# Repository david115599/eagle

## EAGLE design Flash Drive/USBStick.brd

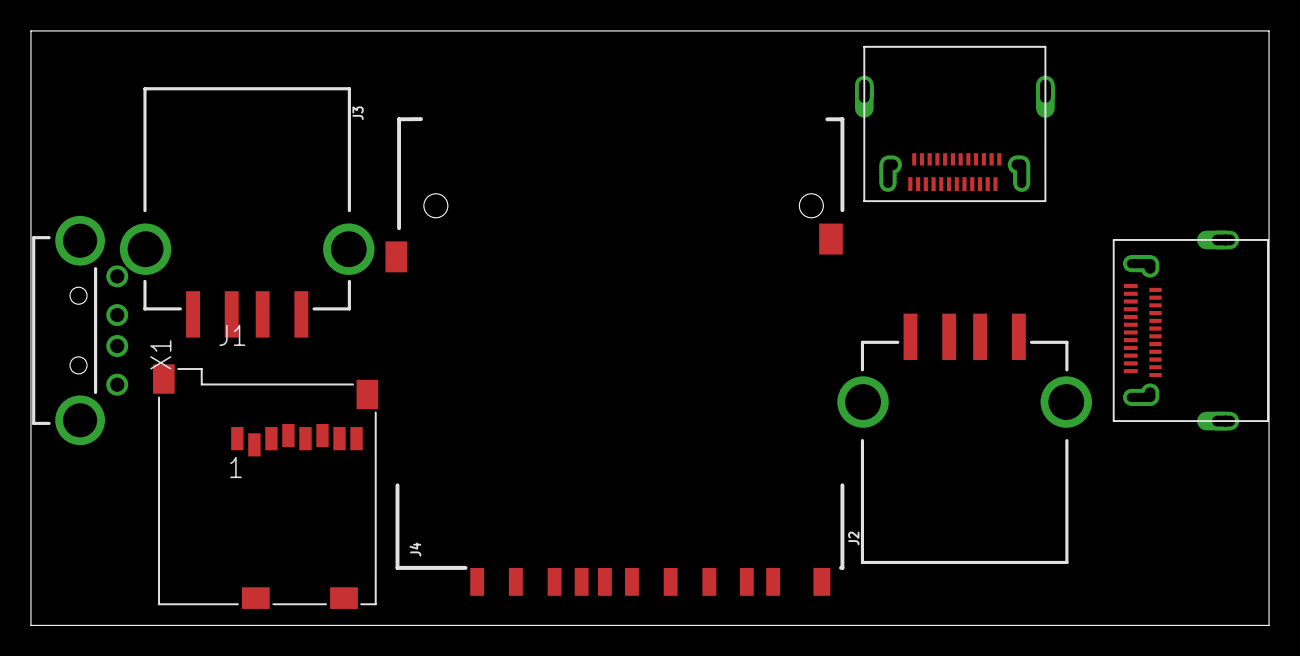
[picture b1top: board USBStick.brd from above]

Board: 2 copper layers, 80.0 x 38.4 mm, 7 parts (0 on the bottom side), 2 nets, no tracks yet.

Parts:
J1: 693071010811
J2, J3: USB_A_SMT_FEMALE; USB-A-S-SILK-FEMALE
J4: SD_CARD_SOCKET; SD
U$1, U$2: USB-TYPE-C; USB-TYPE-C-SMT
X1: USB-A-H

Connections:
GND: J2.GND, J3.GND, U$1.1, U$1.12, U$1.B1, U$1.B12, U$2.1, U$2.12, U$2.B1, U$2.B12
VBUS: J2.VBUS, J3.VBUS

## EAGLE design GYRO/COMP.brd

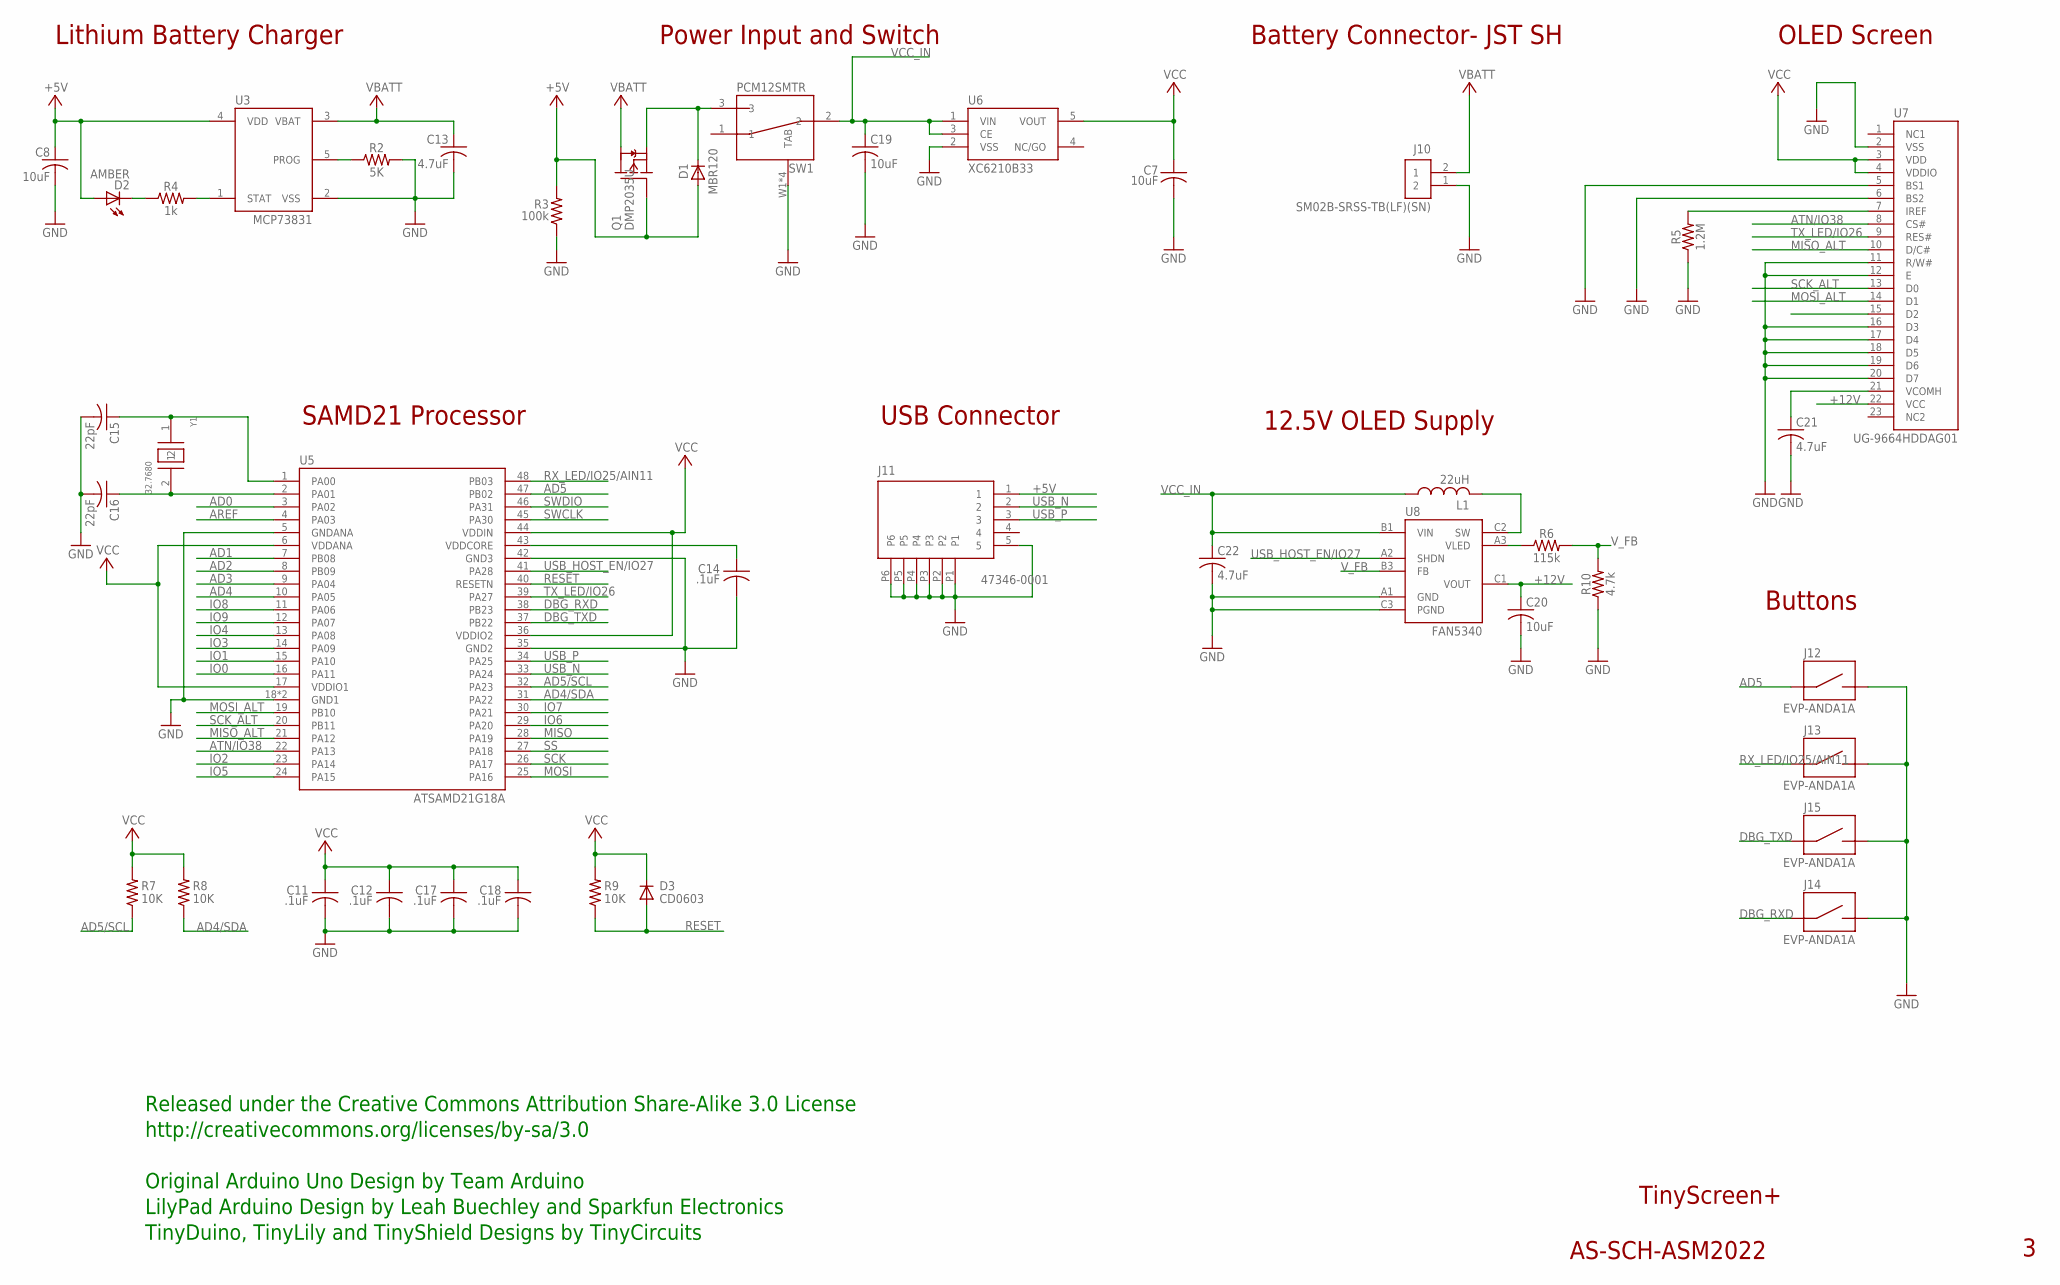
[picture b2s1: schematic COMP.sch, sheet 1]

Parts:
C7, C8: 10uF; C0603; MPN C0603X5R1A104K030BC
C11, C12, C14, C17, C18: .1uF; C0402; MPN GRM155R61C104KA88D
C13: 4.7uF; C0603; MPN C0603X5R0J474K030BC
C15, C16: 22pF; C0402; MPN C0402C220C5GACTU
C19, C20: 10uF; C0805; MPN LMK212BJ106KG-T
C21: 4.7uF; 1206_CAP_TANT; MPN TAJA475K020RNJ
C22: 4.7uF; C0402; MPN C0402C475M9PACTU
D1: MBR120; SOD-123FL; MPN MBR120LSFT1G
D2: AMBER; LNJ_LED; MPN LNJ426W83RA1
D3: CD0603; 0603; MPN CD0603-S01575
J10: SM02B-SRSS-TB(LF)(SN); JST_SH_2X1; MPN SM02B-SRSS-TB (LF)(SN)
J11: 47346-0001; MICRO_USB; MPN 47346-0001
J12, J13, J14, J15: EVP-ANDA1A; PTS840GKP; MPN EVP-ANDA1A
L1: 22uH; R0805; PARTNO AS-ITM-00281
Q1: DMP2035U; SOT23; MPN DMP2035U
R2: 5K; 0402
R3: 100k; 0402; MPN CRG0402J100K/10
R4: 1k; 0402; MPN CRCW04021K00FKTD
R5: 1.2M; 0402; PARTNO AS-ITM-00280
R6: 115k; 0402; MPN CPF0402B115KE1
R7, R8, R9: 10K; 0402; MPN TNPW040210K0BEED
R10: 4.7k; 0402; MPN 373-4.7K
SW1: PCM12SMTR
U3: MCP73831; SOT-23
U5: ATSAMD21G18A; QFN48; PARTNO AS-ITM-00273
U6: XC6210B33; SOT-25
U7: UG-9664HDDAG01; OLED_DISPLAY
U8: FAN5340; WLCSP8_1_57X1_57
Y1: 32.7680; ABS06; PARTNO AS-ITM-00279

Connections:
+5V: C8.1, D1.A, D2.A, J11.1, Q1.B (G), R3.2, U3.4 (VDD)
+12V: C20.1, U7.22 (VCC), U8.C1 (VOUT)
AD0: U5.3 (PA02)
AD1: U5.7 (PB08)
AD2: U5.8 (PB09)
AD3: U5.9 (PA04)
AD4: U5.10 (PA05)
AD4/SDA: R8.1, U5.31 (PA22); also elsewhere on the board
AD5: J12.1, J12.2 (1), U5.47 (PB02)
AD5/SCL: R7.1, U5.32 (PA23); also elsewhere on the board
AREF: U5.4 (PA03)
ATN/IO38: U5.22 (PA13), U7.8 (CS#)
DBG_RXD: J14.1, J14.2 (1), U5.38 (PB23)
DBG_TXD: J15.1, J15.2 (1), U5.37 (PB22)
GND: C7.2, C8.2, C11.2, C12.2, C13.2, C14.2, C15.2, C16.2, C17.2, C18.2, C19.2, C20.2, C21.2, C22.2, J10.1 (2), J11.5, J11.P1, J11.P2, J11.P3, J11.P4, J11.P5, J11.P6, J12.3 (2), J12.4 (2), J13.3 (2), J13.4 (2), J14.3 (2), J14.4 (2), J15.3 (2), J15.4 (2), R2.2, R3.1, R5.1, R10.1, SW1.W1 (TAB), SW1.W2 (TAB), SW1.W3 (TAB), SW1.W4 (TAB), U3.2 (VSS), U5.5 (GNDANA), U5.18 (GND1), U5.35 (GND2), U5.42 (GND3), U5.EXP (GND1), U6.2 (VSS), U7.2 (VSS), U7.5 (BS1), U7.6 (BS2), U7.11 (R/W#), U7.12 (E), U7.16 (D3), U7.17 (D4), U7.18 (D5), U7.19 (D6), U7.20 (D7), U8.A1 (GND), U8.C3 (PGND); also elsewhere on the board
IO0: U5.16 (PA11)
IO1: U5.15 (PA10)
IO2: U5.23 (PA14)
IO3: U5.14 (PA09)
IO4: U5.13 (PA08)
IO5: U5.24 (PA15)
IO6: U5.29 (PA20)
IO7: U5.30 (PA21)
IO8: U5.11 (PA06)
IO9: U5.12 (PA07)
MISO: U5.28 (PA19)
MISO_ALT: U5.21 (PA12), U7.10 (D/C#)
MOSI: U5.25 (PA16)
MOSI_ALT: U5.19 (PB10), U7.14 (D1)
unnamed: D1.C, Q1.E (S), SW1.3
unnamed: C15.1, U5.1 (PA00), Y1.1
unnamed: D2.C, R4.1
unnamed: R2.1, U3.5 (PROG)
unnamed: R4.2, U3.1 (STAT)
unnamed: C16.1, U5.2 (PA01), Y1.2
unnamed: C14.1, U5.43 (VDDCORE)
unnamed: L1.2, U8.C2 (SW)
unnamed: R5.2, U7.7 (IREF)
unnamed: C21.1, U7.21 (VCOMH)
unnamed: R6.1, U8.A3 (VLED)
RESET: D3.A, R9.1, U5.40 (RESETN)
RX_LED/IO25/AIN11: J13.1, J13.2 (1), U5.48 (PB03)
SCK: U5.26 (PA17)
SCK_ALT: U5.20 (PB11), U7.13 (D0)
SS: U5.27 (PA18)
SWCLK: U5.45 (PA30)
SWDIO: U5.46 (PA31)
TX_LED/IO26: U5.39 (PA27), U7.9 (RES#)
USB_HOST_EN/IO27: U5.41 (PA28), U8.A2 (SHDN)
USB_N: J11.2, U5.33 (PA24)
USB_P: J11.3, U5.34 (PA25)
VBATT: C13.1, J10.2 (1), Q1.C (D), U3.3 (VBAT)
VCC: C7.1, C11.1, C12.1, C17.1, C18.1, D3.C, R7.2, R8.2, R9.2, U5.6 (VDDANA), U5.17 (VDDIO1), U5.36 (VDDIO2), U5.44 (VDDIN), U6.5 (VOUT), U7.3 (VDD), U7.4 (VDDIO); also elsewhere on the board
VCC_IN: C19.1, C22.1, L1.1, SW1.2, U6.1 (VIN), U6.3 (CE), U8.B1 (VIN)
V_FB: R6.2, R10.2, U8.B3 (FB)

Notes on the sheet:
SAMD21 Processor
Power Input and Switch
TinyScreen+
AS-SCH-ASM2022
Released under the Creative Commons Attribution Share-Alike 3.0 License
http://creativecommons.org/licenses/by-sa/3.0
Original Arduino Uno Design by Team Arduino
TinyDuino, TinyLily and TinyShield Designs by TinyCircuits
LilyPad Arduino Design by Leah Buechley and Sparkfun Electronics
Lithium Battery Charger
Battery Connector- JST SH
OLED Screen
12.5V OLED Supply
Buttons
USB Connector

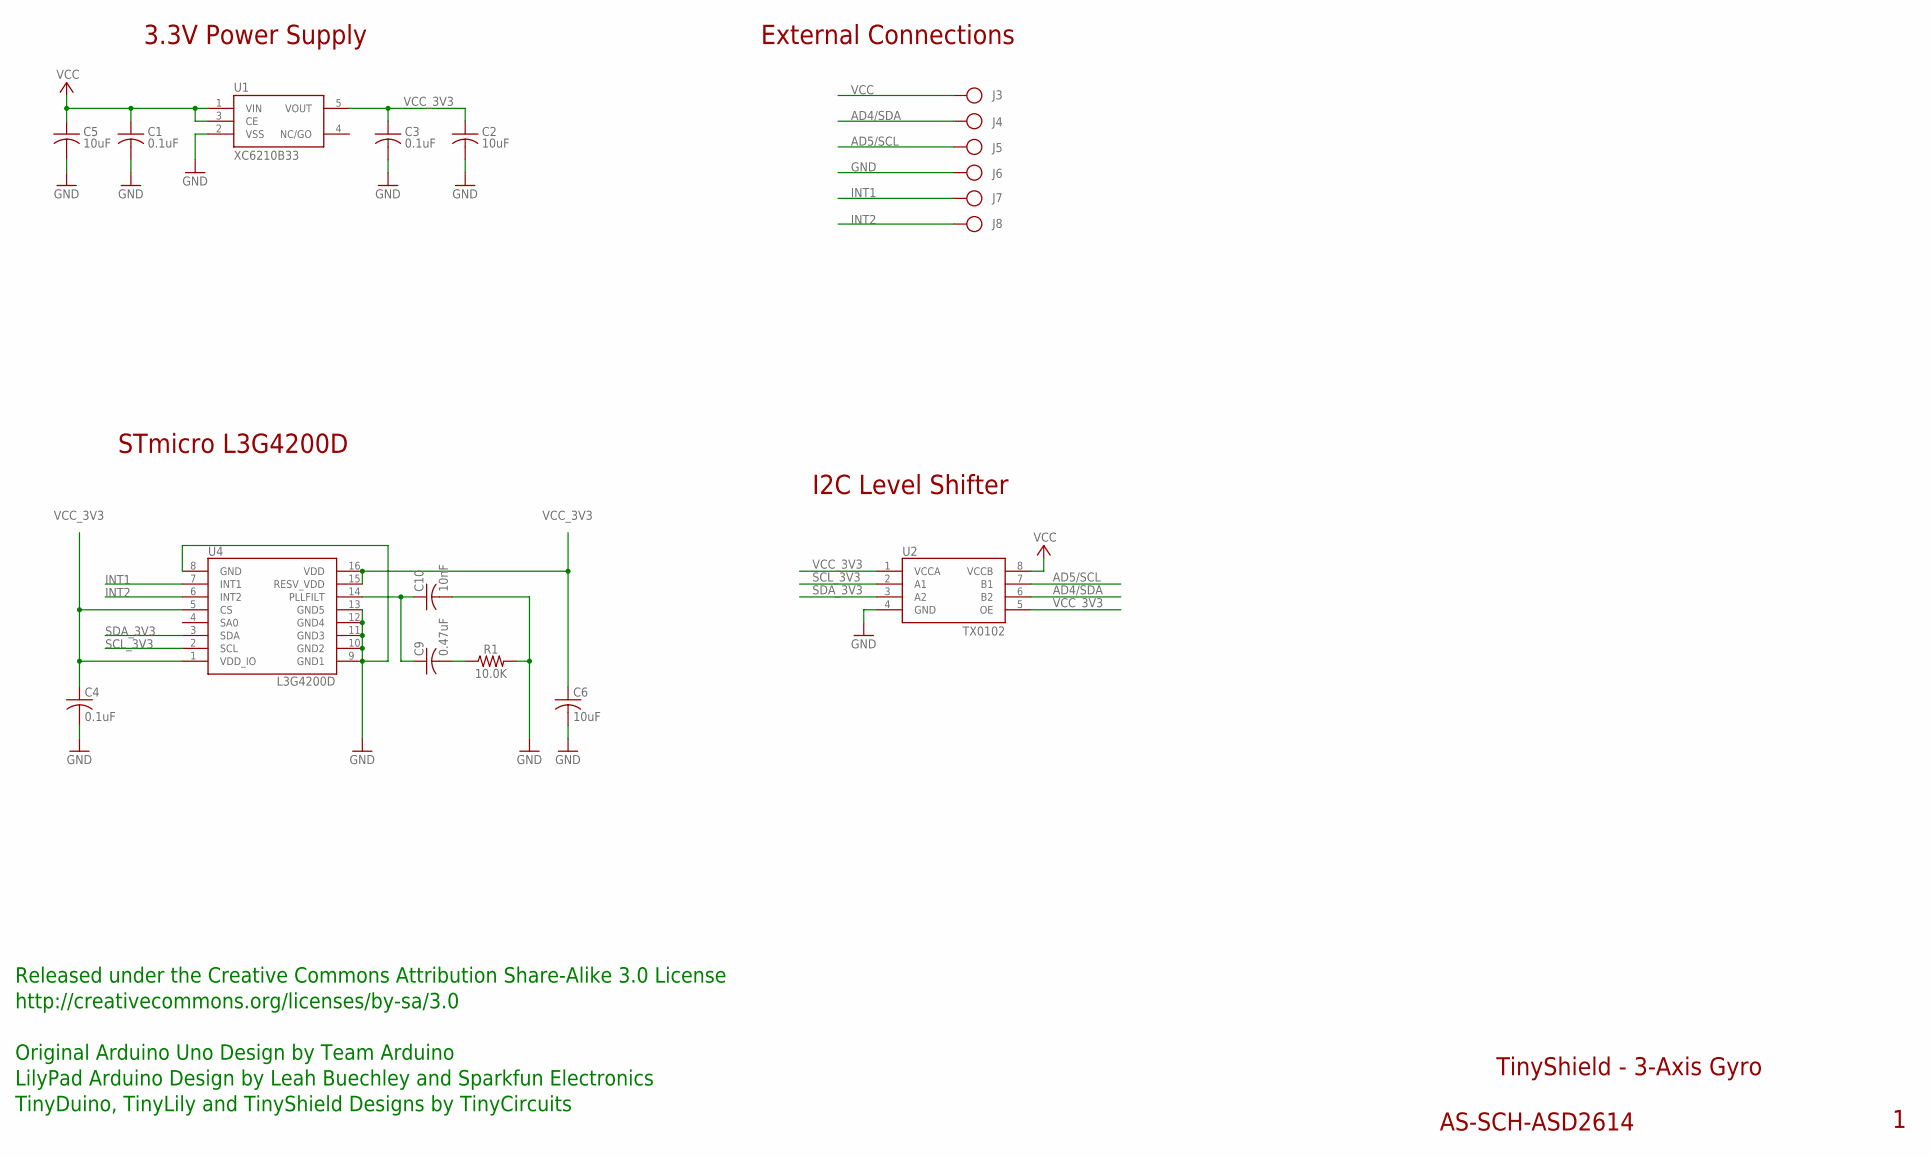
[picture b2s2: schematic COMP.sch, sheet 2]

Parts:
C1, C3, C4: 0.1uF; C0402; MPN GRM155R61A104JA01D
C2, C5: 10uF; C0805; MPN LMK212BJ106KG-T
C6: 10uF; C0603; MPN C0603X5R1A104K030BC
C9: 0.47uF; C0402@1; MPN GRM155R60J474KE19D
C10: 10nF; 0402@1; MPN VJ0402V103ZXACW1BC
J3, J4, J5, J6, J7, J8: PIN_1X.1"; 1X.1"
R1: 10.0K; 0402; MPN CRCW120610K0FKTA
U1: XC6210B33; SOT-25
U2: TX0102; DQE(R-PX2SON-N8)
U4: L3G4200D

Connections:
AD4/SDA: J4.1, U2.6 (B2); also elsewhere on the board
AD5/SCL: J5.1, U2.7 (B1); also elsewhere on the board
GND: C1.2, C2.2, C3.2, C4.2, C5.2, C6.2, C10.2, J6.1, R1.2, U1.2 (VSS), U2.4 (GND), U4.8 (GND), U4.9 (GND1), U4.10 (GND2), U4.11 (GND3), U4.12 (GND4), U4.13 (GND5); also elsewhere on the board
INT1: J7.1, U4.7 (INT1)
INT2: J8.1, U4.6 (INT2)
unnamed: C9.2, R1.1
unnamed: C9.1, C10.1, U4.14 (PLLFILT)
SCL_3V3: U2.2 (A1), U4.2 (SCL)
SDA_3V3: U2.3 (A2), U4.3 (SDA)
VCC: C1.1, C5.1, J3.1, U1.1 (VIN), U1.3 (CE), U2.8 (VCCB); also elsewhere on the board
VCC_3V3: C2.1, C3.1, C4.1, C6.1, U1.5 (VOUT), U2.1 (VCCA), U2.5 (OE), U4.1 (VDD_IO), U4.5 (CS), U4.15 (RESV_VDD), U4.16 (VDD)

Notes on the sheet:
TinyShield - 3-Axis Gyro
AS-SCH-ASD2614
Released under the Creative Commons Attribution Share-Alike 3.0 License
http://creativecommons.org/licenses/by-sa/3.0
LilyPad Arduino Design by Leah Buechley and Sparkfun Electronics
TinyDuino, TinyLily and TinyShield Designs by TinyCircuits
Original Arduino Uno Design by Team Arduino
External Connections
3.3V Power Supply
I2C Level Shifter
STmicro L3G4200D

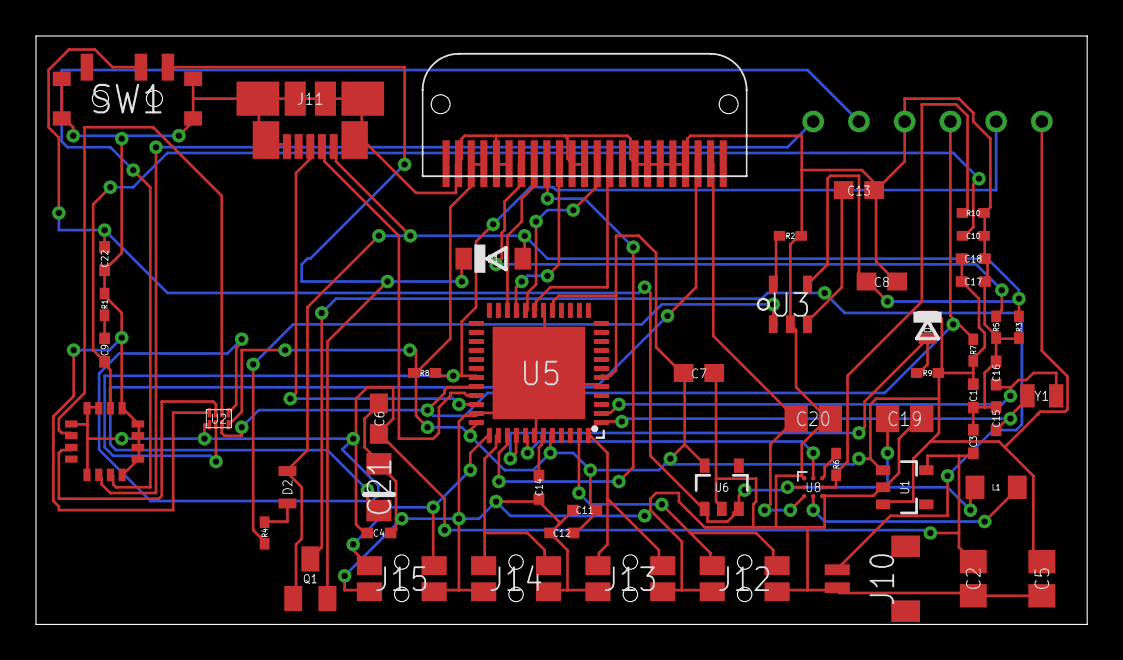
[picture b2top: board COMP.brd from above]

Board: 2 copper layers, 58.4 x 32.7 mm, 59 parts (0 on the bottom side), 40 nets.

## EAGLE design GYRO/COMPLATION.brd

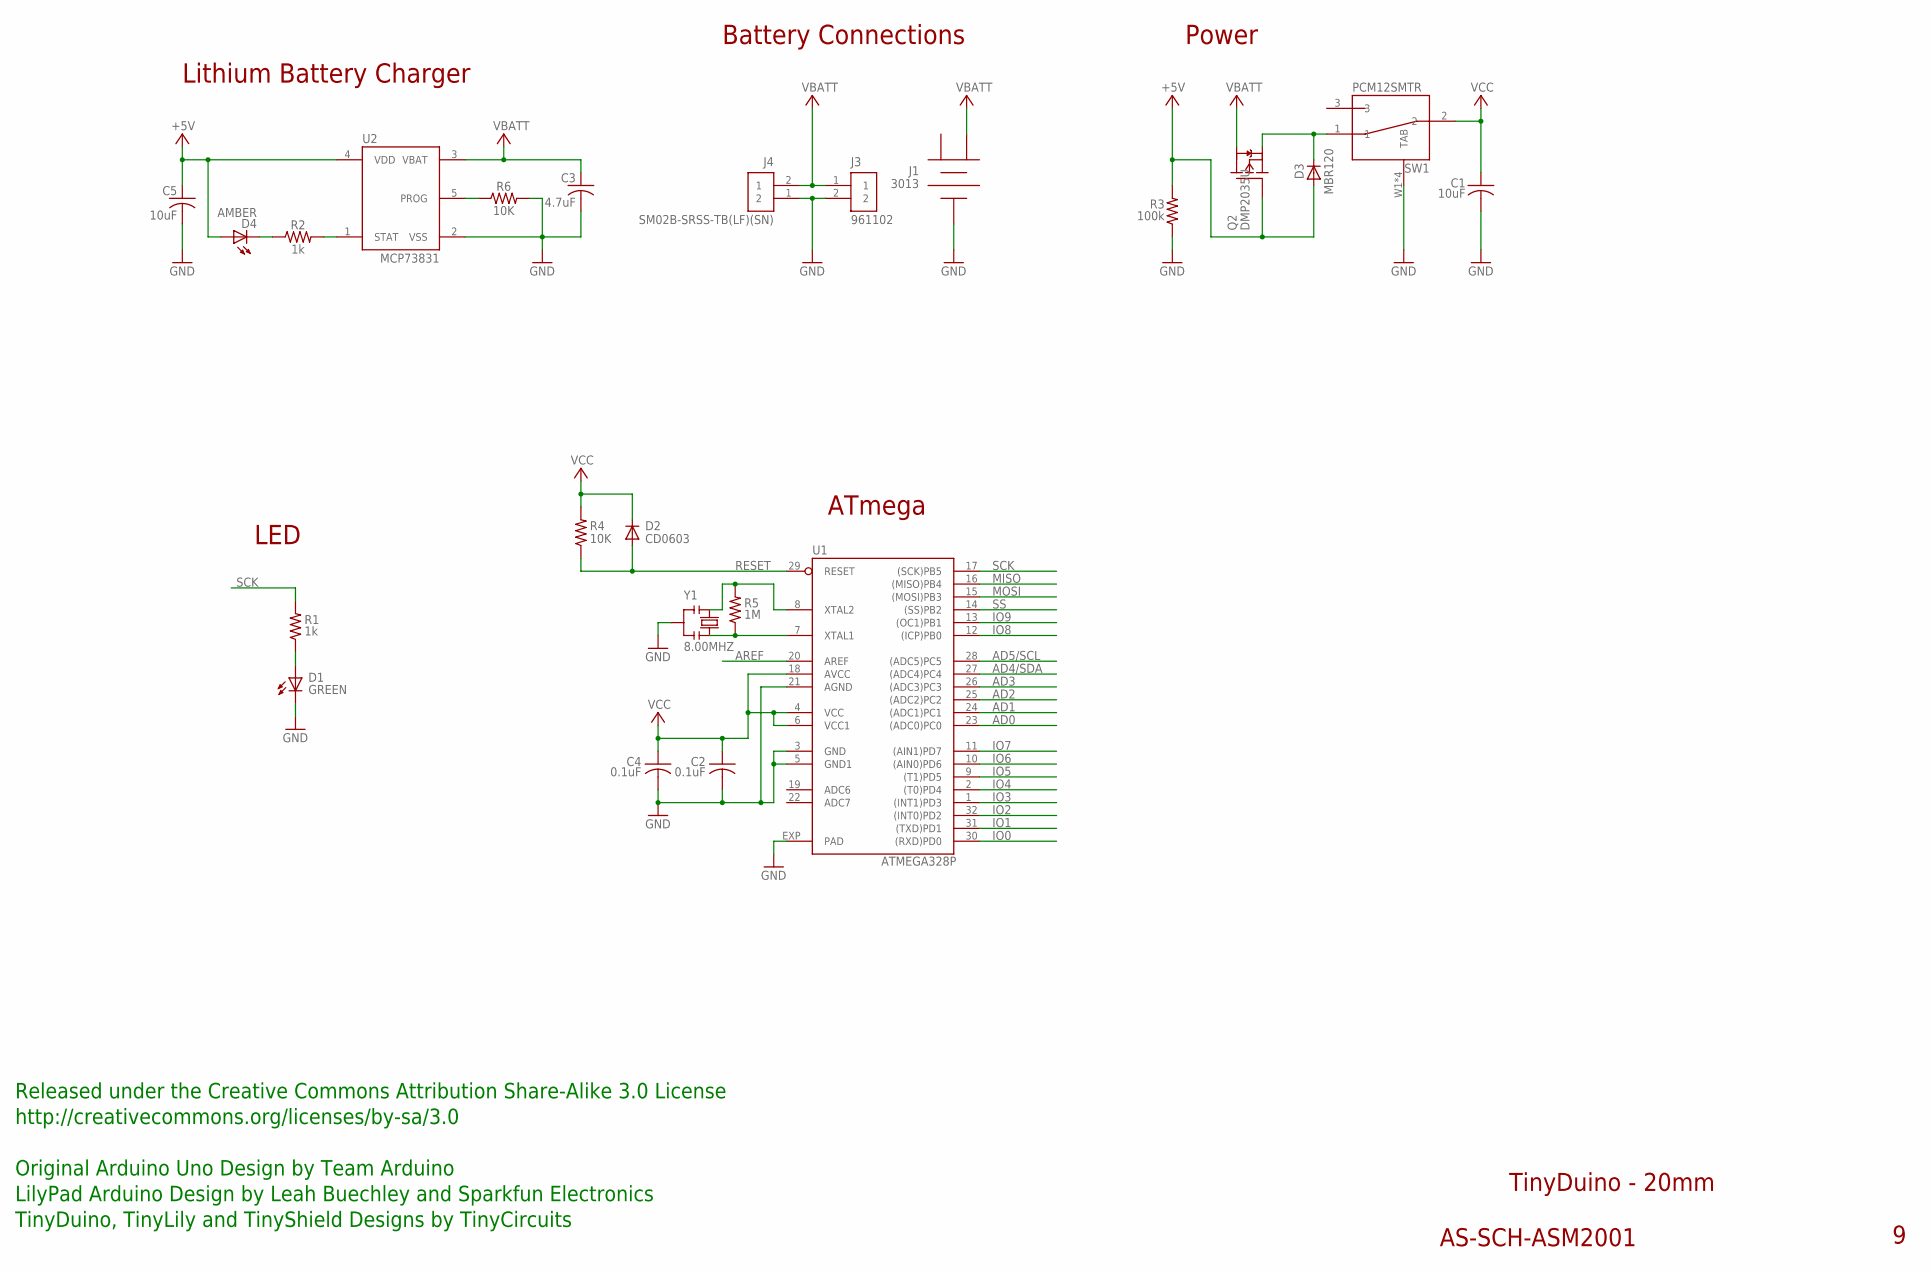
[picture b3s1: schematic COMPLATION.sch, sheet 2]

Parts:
C1, C5: 10uF; C0603; PARTNO AS-ITM-00002
C2, C4: 0.1uF; C0402; PARTNO AS-ITM-00008
C3: 4.7uF; C0402@1; PARTNO AS-ITM-00242
D1: GREEN; LNJ_LED; PARTNO AS-ITM-00011
D2: CD0603; 0603; PARTNO AS-ITM-00009
D3: MBR120; SOD-123FL
D4: AMBER; LNJ_LED; PARTNO AS-ITM-00026
J1: 3013; PARTNO AS-ITM-00001
J3: 961102; 2X.1"
J4: SM02B-SRSS-TB(LF)(SN); JST_SH_2X1
Q2: DMP2035U; SOT23
R1, R2: 1k; 0402; PARTNO AS-ITM-00003
R3: 100k; 0402; PARTNO AS-ITM-00004
R4: 10K; 0402; PARTNO AS-ITM-00032
R5: 1M; 0402; PARTNO AS-ITM-00005
R6: 10K; 0402
SW1: PCM12SMTR
U1: ATMEGA328P; ATMEL_QFN32; PARTNO AS-ITM-00013
U2: MCP73831; SOT-23
Y1: 8.00MHZ; RESONATOR_SMALL; PARTNO AS-ITM-00027

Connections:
1: J1.1
+5V: C5.1, D3.A, D4.A, Q2.B (G), R3.2, U2.4 (VDD); also elsewhere on the board
AD0: U1.23 ((ADC0)PC0)
AD1: U1.24 ((ADC1)PC1)
AD2: U1.25 ((ADC2)PC2)
AD3: U1.26 ((ADC3)PC3)
AD4/SDA: U1.27 ((ADC4)PC4); also elsewhere on the board
AD5/SCL: U1.28 ((ADC5)PC5); also elsewhere on the board
AREF: U1.20 (AREF)
GND: C1.2, C2.2, C3.2, C4.2, C5.2, D1.C, J1.3, J3.2, J4.1 (2), R3.1, R6.2, SW1.W1 (TAB), SW1.W2 (TAB), SW1.W3 (TAB), SW1.W4 (TAB), U1.3 (GND), U1.5 (GND1), U1.21 (AGND), U1.EXP (PAD), U2.2 (VSS), Y1.2; also elsewhere on the board
IO0: U1.30 ((RXD)PD0); also elsewhere on the board
IO1: U1.31 ((TXD)PD1); also elsewhere on the board
IO2: U1.32 ((INT0)PD2)
IO3: U1.1 ((INT1)PD3)
IO4: U1.2 ((T0)PD4)
IO5: U1.9 ((T1)PD5)
IO6: U1.10 ((AIN0)PD6)
IO7: U1.11 ((AIN1)PD7)
IO8: U1.12 ((ICP)PB0)
IO9: U1.13 ((OC1)PB1)
MISO: U1.16 ((MISO)PB4)
MOSI: U1.15 ((MOSI)PB3)
unnamed: R5.2, U1.8 (XTAL2), Y1.1
unnamed: D3.C, Q2.E (S), SW1.1
unnamed: R5.1, U1.7 (XTAL1), Y1.3
unnamed: D1.A, R1.1
unnamed: D4.C, R2.1
unnamed: R6.1, U2.5 (PROG)
unnamed: R2.2, U2.1 (STAT)
RESET: D2.A, R4.1, U1.29 (RESET); also elsewhere on the board
SCK: R1.2, U1.17 ((SCK)PB5)
SS: U1.14 ((SS)PB2)
VBATT: C3.1, J1.2, J3.1, J4.2 (1), Q2.C (D), U2.3 (VBAT)
VCC: C1.1, C2.1, C4.1, D2.C, R4.2, SW1.2, U1.4 (VCC), U1.6 (VCC1), U1.18 (AVCC); also elsewhere on the board

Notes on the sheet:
ATmega
Power
LED
TinyDuino - 20mm
AS-SCH-ASM2001
Released under the Creative Commons Attribution Share-Alike 3.0 License
http://creativecommons.org/licenses/by-sa/3.0
Original Arduino Uno Design by Team Arduino
TinyDuino, TinyLily and TinyShield Designs by TinyCircuits
LilyPad Arduino Design by Leah Buechley and Sparkfun Electronics
Lithium Battery Charger
Battery Connections

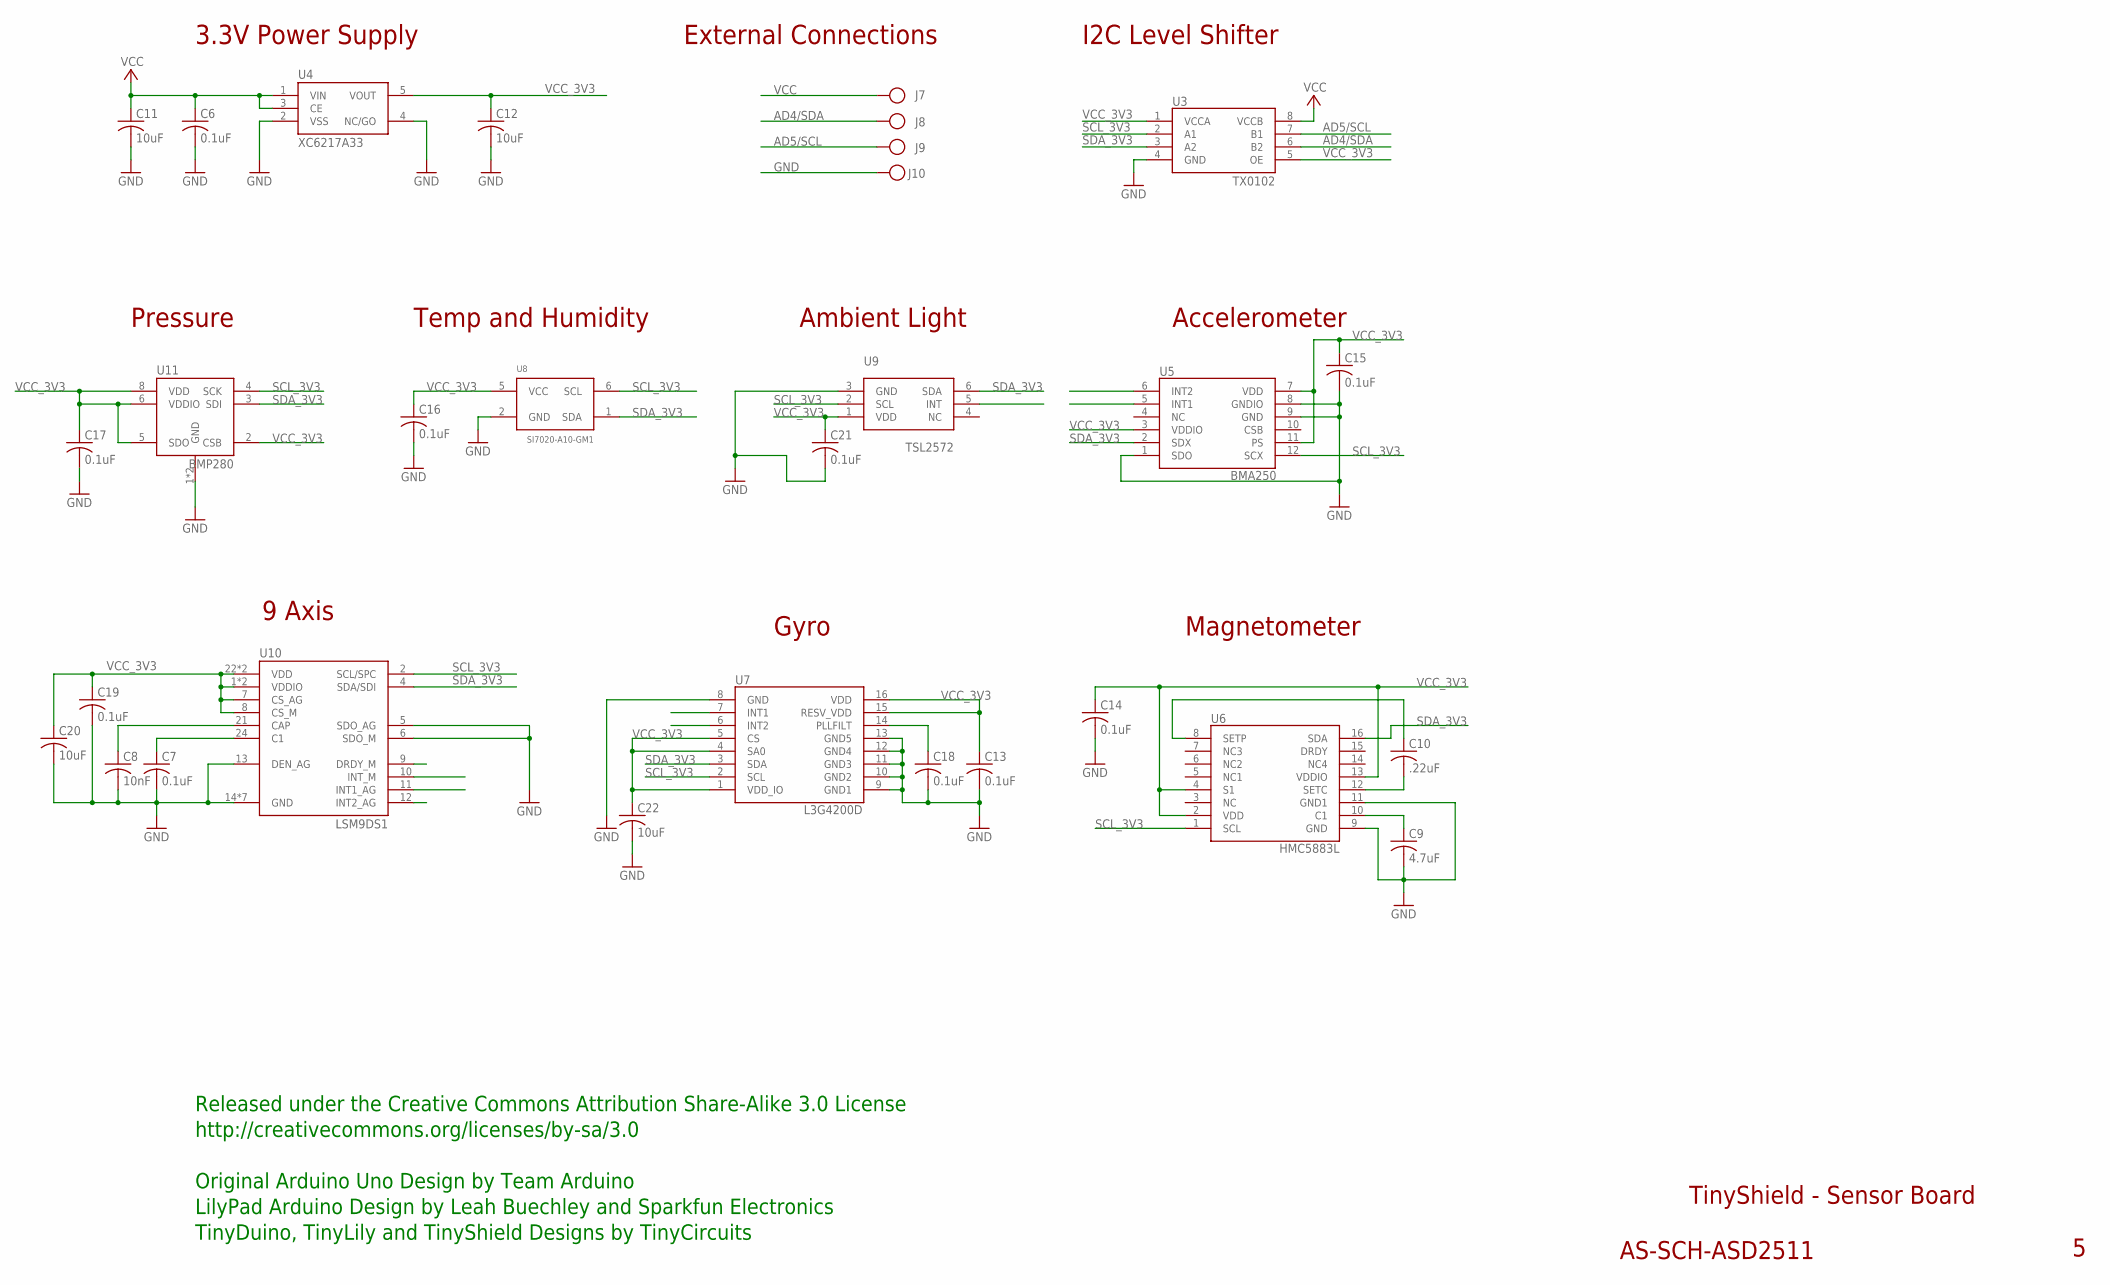
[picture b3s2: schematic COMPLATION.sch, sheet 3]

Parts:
C6, C13, C14, C15, C16, C17, C18, C19, C21: 0.1uF; C0402; PARTNO AS-ITM-00008
C7: 0.1uF; C0402
C8: 10nF; C0402@1
C9: 4.7uF; C0402@1; PARTNO AS-ITM-00242
C10: .22uF; C0402@1
C11, C22: 10uF; C0603
C12, C20: 10uF; C0603; PARTNO AS-ITM-00002
J7, J8, J9, J10: PIN_1X.1"1; 1X.1"_2
U3: TX0102; DQE(R-PX2SON-N8)
U4: XC6217A33; SOT-25; PARTNO AS-ITM-00249
U5: BMA250; 3-AXIS_ACCELEROMETER
U6: HMC5883L
U7: L3G4200D
U8: SI7020-A10-GM1; DFN6
U9: TSL2572
U10: LSM9DS1; LGA-24
U11: BMP280

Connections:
AD4/SDA: J8.1, U3.6 (B2); also elsewhere on the board
AD5/SCL: J9.1, U3.7 (B1); also elsewhere on the board
GND: C6.2, C7.2, C8.2, C9.2, C11.2, C12.2, C13.2, C14.2, C15.2, C16.2, C17.2, C18.2, C19.2, C20.2, C21.2, C22.2, J10.1, U3.4 (GND), U4.2 (VSS), U4.4 (NC/GO), U5.1 (SDO), U5.8 (GNDIO), U5.9 (GND), U6.9 (GND), U6.11 (GND1), U7.8 (GND), U7.9 (GND1), U7.10 (GND2), U7.11 (GND3), U7.12 (GND4), U7.13 (GND5), U8.2 (GND), U9.3 (GND), U10.5 (SDO_AG), U10.6 (SDO_M), U10.13 (DEN_AG), U10.14 (GND), U10.15 (GND), U10.16 (GND), U10.17 (GND), U10.18 (GND), U10.19 (GND), U10.20 (GND), U11.1 (GND), U11.7 (GND); also elsewhere on the board
unnamed: C9.1, U6.10 (C1)
unnamed: C10.2, U6.12 (SETC)
unnamed: C10.1, U6.8 (SETP)
unnamed: C18.1, U7.14 (PLLFILT)
unnamed: C8.1, U10.21 (CAP)
unnamed: C7.1, U10.24 (C1)
SCL_3V3: U3.2 (A1), U5.12 (SCX), U6.1 (SCL), U7.2 (SCL), U8.6 (SCL), U9.2 (SCL), U10.2 (SCL/SPC), U11.4 (SCK)
SDA_3V3: U3.3 (A2), U5.2 (SDX), U6.16 (SDA), U7.3 (SDA), U8.1 (SDA), U9.6 (SDA), U10.4 (SDA/SDI), U11.3 (SDI)
VCC: C6.1, C11.1, J7.1, U3.8 (VCCB), U4.1 (VIN), U4.3 (CE); also elsewhere on the board
VCC_3V3: C12.1, C13.1, C14.1, C15.1, C16.1, C17.1, C19.1, C20.1, C21.1, C22.1, U3.1 (VCCA), U3.5 (OE), U4.5 (VOUT), U5.3 (VDDIO), U5.7 (VDD), U5.11 (PS), U6.2 (VDD), U6.4 (S1), U6.13 (VDDIO), U7.1 (VDD_IO), U7.4 (SA0), U7.5 (CS), U7.15 (RESV_VDD), U7.16 (VDD), U8.5 (VCC), U9.1 (VDD), U10.1 (VDDIO), U10.3 (VDDIO), U10.7 (CS_AG), U10.8 (CS_M), U10.22 (VDD), U10.23 (VDD), U11.2 (CSB), U11.5 (SDO), U11.6 (VDDIO), U11.8 (VDD)

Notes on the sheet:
TinyShield - Sensor Board
AS-SCH-ASD2511
Released under the Creative Commons Attribution Share-Alike 3.0 License
http://creativecommons.org/licenses/by-sa/3.0
LilyPad Arduino Design by Leah Buechley and Sparkfun Electronics
TinyDuino, TinyLily and TinyShield Designs by TinyCircuits
Original Arduino Uno Design by Team Arduino
External Connections
3.3V Power Supply
I2C Level Shifter
9 Axis
Pressure
Temp and Humidity
Ambient Light
Accelerometer
Gyro
Magnetometer

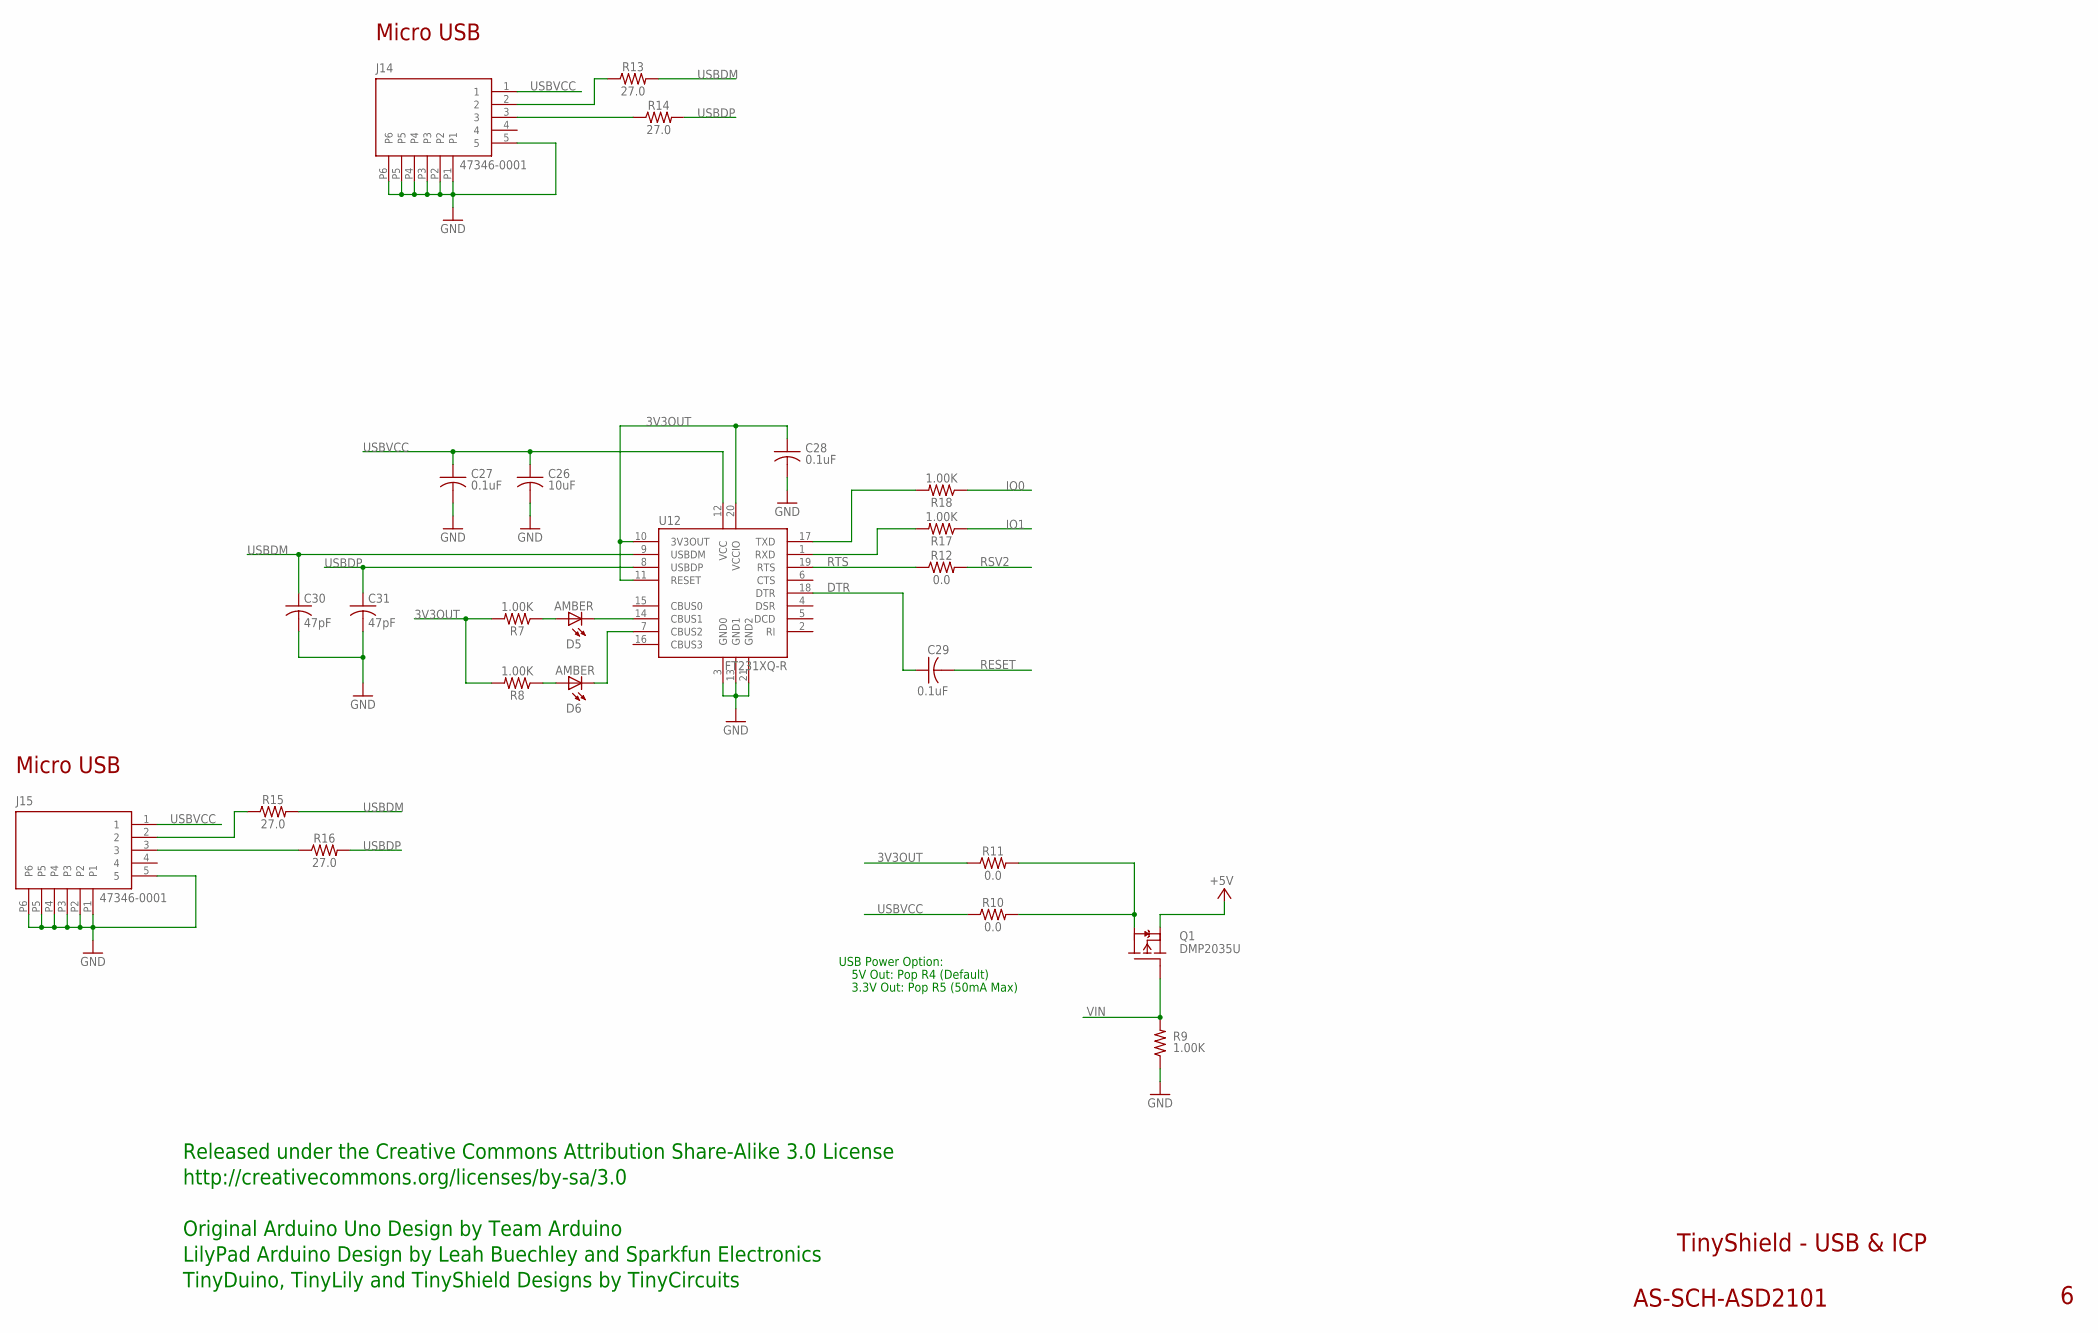
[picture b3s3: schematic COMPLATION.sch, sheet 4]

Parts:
C26: 10uF; C0603
C27: 0.1uF; C0402
C28, C29: 0.1uF; C0402; PARTNO AS-ITM-00008
C30, C31: 47pF; 0402; PARTNO AS-ITM-00241
D5, D6: AMBER; LNJ_LED
J14, J15: 47346-0001; MICRO_USB; PARTNO AS-ITM-00021
Q1: DMP2035U; SOT23
R7, R8, R9: 1.00K; 0402
R10, R11: 0.0; 0402
R12: 0.0; 0402_SHORT
R13, R14, R15, R16: 27.0; 0402
R17, R18: 1.00K; 0402; PARTNO AS-ITM-00003
U12: FT231XQ-R; QFN20

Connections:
3V3OUT: C28.1, R7.2, R8.2, R11.1, U12.10 (3V3OUT), U12.11 (RESET), U12.20 (VCCIO)
+5V: Q1.E (S); also elsewhere on the board
DTR: C29.1, U12.18 (DTR)
GND: C26.2, C27.2, C28.2, C30.2, C31.2, J14.5, J14.P1, J14.P2, J14.P3, J14.P4, J14.P5, J14.P6, J15.5, J15.P1, J15.P2, J15.P3, J15.P4, J15.P5, J15.P6, R9.1, U12.3 (GND0), U12.13 (GND1), U12.21 (GND2); also elsewhere on the board
IO0: R18.1; also elsewhere on the board
IO1: R17.1; also elsewhere on the board
unnamed: D5.C, U12.14 (CBUS1)
unnamed: D6.C, U12.7 (CBUS2)
unnamed: D5.A, R7.1
unnamed: D6.A, R8.1
unnamed: Q1.C (D), R10.2, R11.2
unnamed: J14.2, R13.1
unnamed: J14.3, R14.1
unnamed: J15.2, R15.1
unnamed: J15.3, R16.1
unnamed: R17.2, U12.1 (RXD)
unnamed: R18.2, U12.17 (TXD)
RESET: C29.2; also elsewhere on the board
RSV2: R12.2
RTS: R12.1, U12.19 (RTS)
USBDM: C30.1, R13.2, R15.2, U12.9 (USBDM)
USBDP: C31.1, R14.2, R16.2, U12.8 (USBDP)
USBVCC: C26.1, C27.1, J14.1, J15.1, R10.1, U12.12 (VCC)
VIN: Q1.B (G), R9.2

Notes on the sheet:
TinyShield - USB & ICP
AS-SCH-ASD2101
Micro USB
Released under the Creative Commons Attribution Share-Alike 3.0 License
http://creativecommons.org/licenses/by-sa/3.0
Original Arduino Uno Design by Team Arduino
TinyDuino, TinyLily and TinyShield Designs by TinyCircuits
LilyPad Arduino Design by Leah Buechley and Sparkfun Electronics
USB Power Option:
5V Out: Pop R4 (Default)
3.3V Out: Pop R5 (50mA Max)

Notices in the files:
parts and their libraries:
Wurth_Elektronik_Electromechanic_Input-O: Copyright: Würth Elektronik
SparkFun-Connectors: Licensing: Creative Commons ShareAlike 4.0 International - https://creativecommons.org/licenses/by-sa/4.0
